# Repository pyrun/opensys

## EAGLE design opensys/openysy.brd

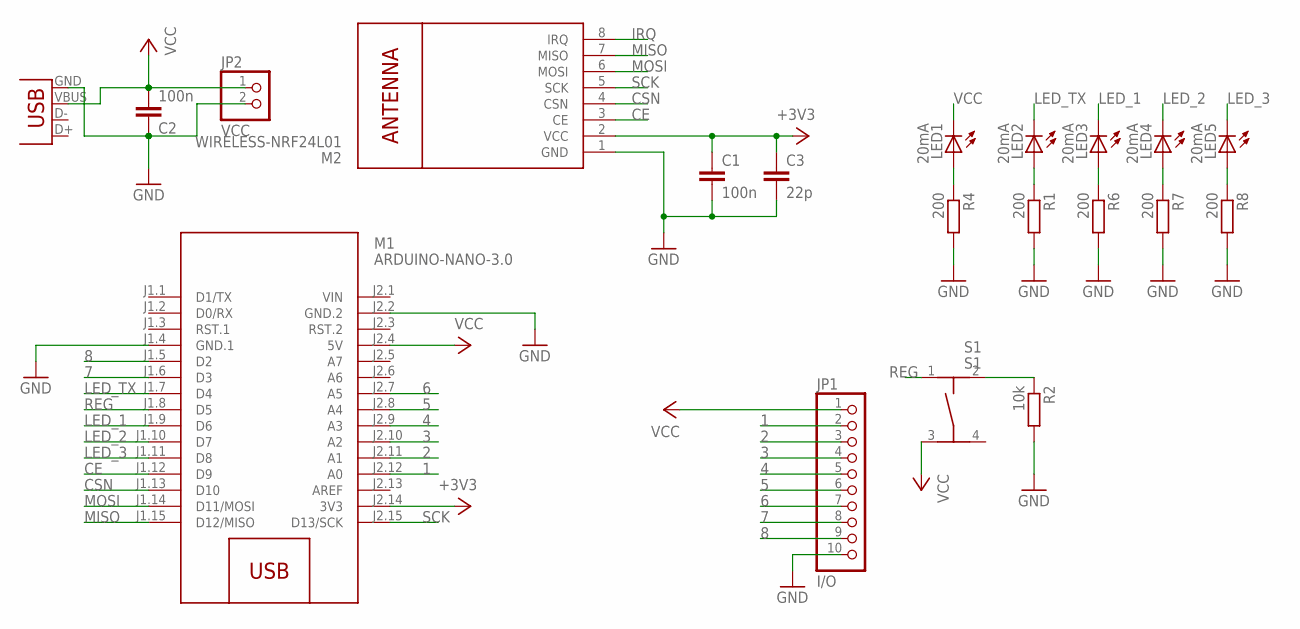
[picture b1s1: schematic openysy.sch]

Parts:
C1, C2: 100n; C1206
C3: 22p; C1206
JP1: I/O; 1X10
JP2: VCC; 1X02
LED1, LED2, LED3, LED4, LED5: 20mA; CHIPLED_1206
M1: ARDUINO-NANO-3.0
M2: WIRELESS-NRF24L01
R1, R4, R6, R7, R8: 200; R1206
R2: 10k; R1206
S1: S1; TASTER-9314_SMD
X2: USBPTH; USB-B-PTH

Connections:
1: JP1.2, M1.J2.12 (A0)
2: JP1.3, M1.J2.11 (A1)
3: JP1.4, M1.J2.10 (A2)
4: JP1.5, M1.J2.9 (A3)
5: JP1.6, M1.J2.8 (A4)
6: JP1.7, M1.J2.7 (A5)
7: JP1.8, M1.J1.6 (D3)
8: JP1.9, M1.J1.5 (D2)
+3V3: C1.1, C3.1, M1.J2.14 (3V3), M2.2 (VCC)
CE: M1.J1.12 (D9), M2.3 (CE)
CSN: M1.J1.13 (D10), M2.4 (CSN)
GND: C1.2, C2.1, C3.2, JP1.10, JP2.2, M1.J1.4 (GND.1), M1.J2.2 (GND.2), M2.1 (GND), R1.2, R2.2, R4.2, R6.2, R7.2, R8.2, X2.GND
IRQ: M2.8 (IRQ)
LED_1: LED3.C, M1.J1.9 (D6)
LED_2: LED4.C, M1.J1.10 (D7)
LED_3: LED5.C, M1.J1.11 (D8)
LED_TX: LED2.C, M1.J1.7 (D4)
MISO: M1.J1.15 (D12/MISO), M2.7 (MISO)
MOSI: M1.J1.14 (D11/MOSI), M2.6 (MOSI)
unnamed: LED2.A, R1.1
unnamed: LED1.A, R4.1
unnamed: R2.1, S1.2
unnamed: LED3.A, R6.1
unnamed: LED4.A, R7.1
unnamed: LED5.A, R8.1
REG: M1.J1.8 (D5), S1.1
SCK: M1.J2.15 (D13/SCK), M2.5 (SCK)
VCC: C2.2, JP1.1, JP2.1, LED1.C, M1.J2.4 (5V), S1.3, X2.VBUS
VIN: M1.J2.1 (VIN)

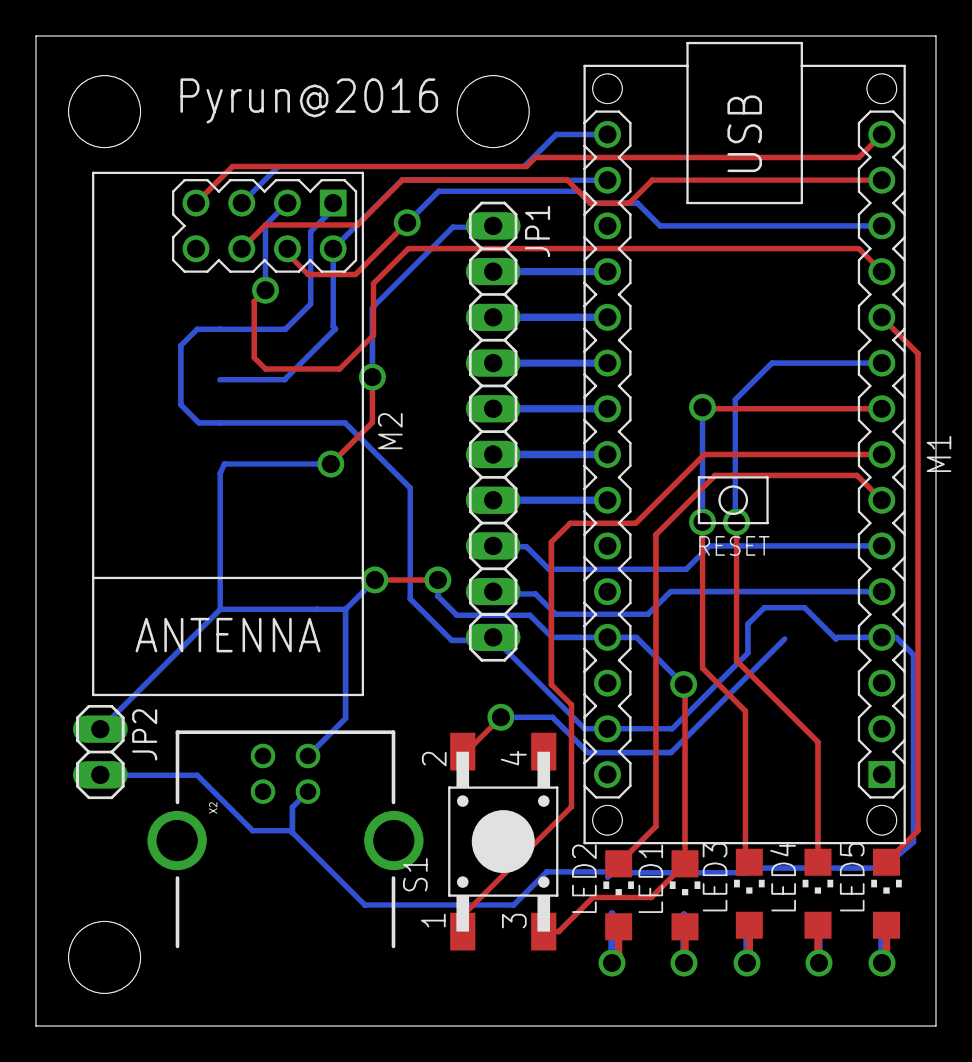
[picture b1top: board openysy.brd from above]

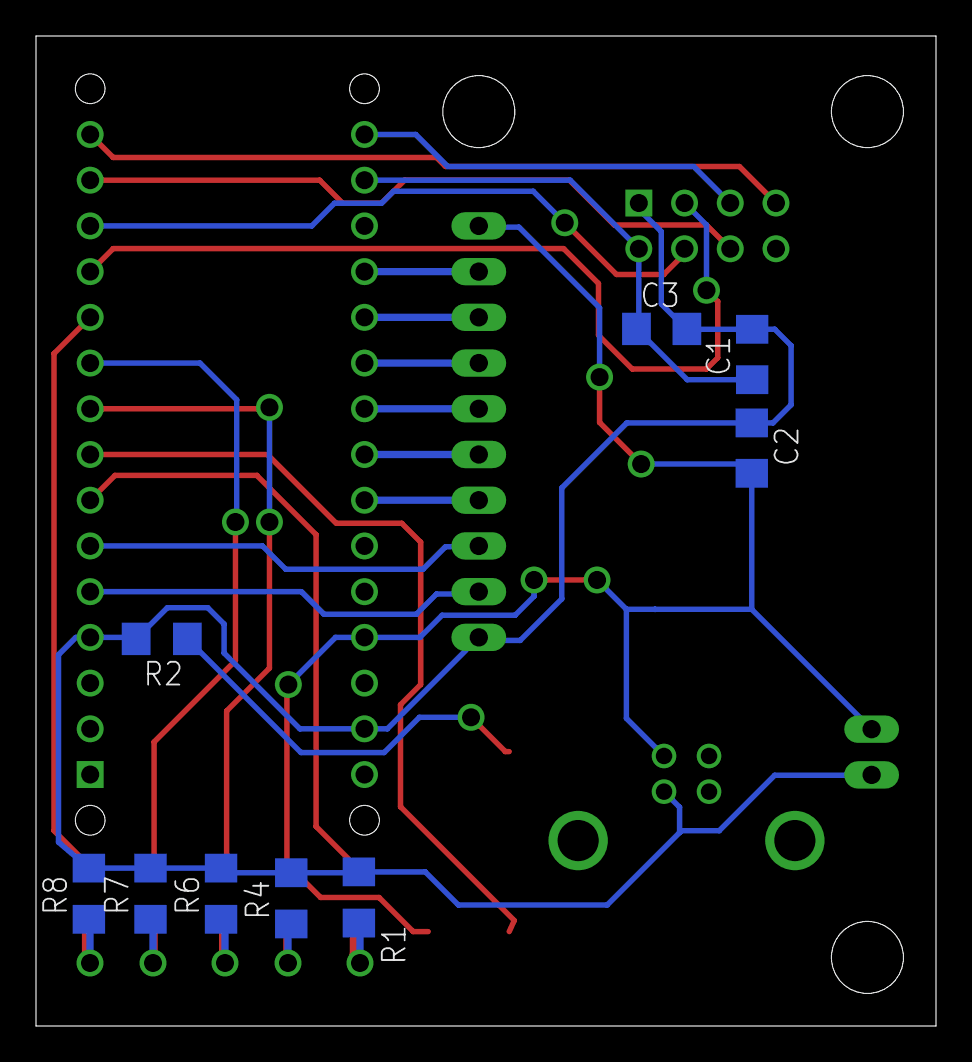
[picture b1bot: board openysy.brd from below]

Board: 2 copper layers, 50.0 x 55.0 mm, 20 parts (9 on the bottom side), 27 nets.

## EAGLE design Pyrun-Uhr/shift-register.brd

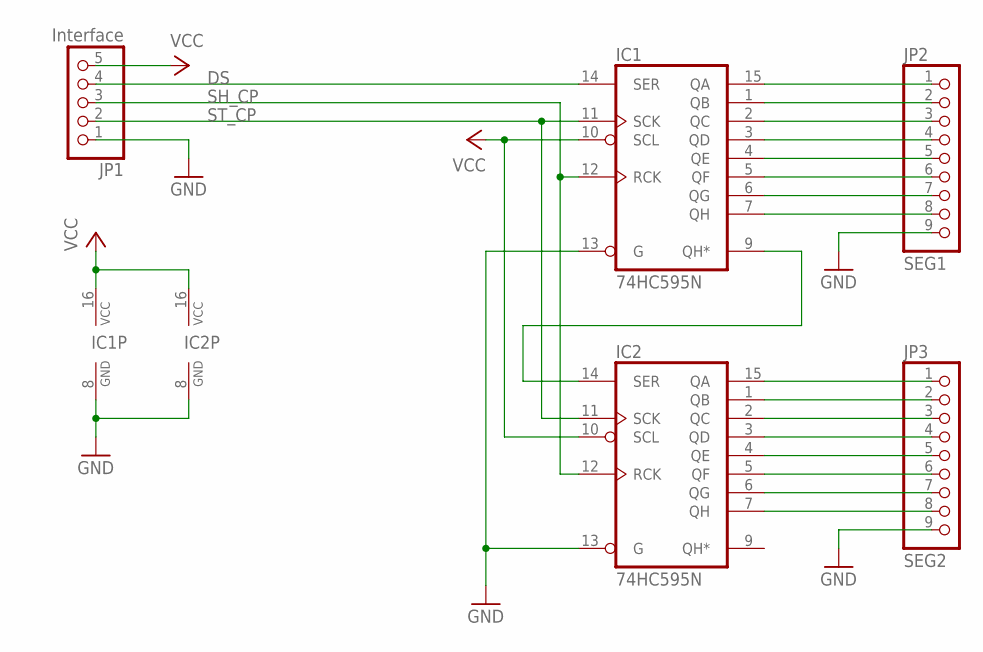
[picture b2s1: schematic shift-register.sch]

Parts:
IC1, IC2: 74HC595N; DIL16
JP1: Interface; 1X05
JP2: SEG1; 1X09
JP3: SEG2; 1X09

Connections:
DS: IC1.14 (SER), JP1.4
GND: IC1.8 (GND), IC1.13 (G), IC2.8 (GND), IC2.13 (G), JP1.1, JP2.9, JP3.9
unnamed: IC1.9 (QH*), IC2.14 (SER)
unnamed: IC1.15 (QA), JP2.1
unnamed: IC1.1 (QB), JP2.2
unnamed: IC1.2 (QC), JP2.3
unnamed: IC1.3 (QD), JP2.4
unnamed: IC1.4 (QE), JP2.5
unnamed: IC1.5 (QF), JP2.6
unnamed: IC1.6 (QG), JP2.7
unnamed: IC1.7 (QH), JP2.8
unnamed: IC2.15 (QA), JP3.1
unnamed: IC2.1 (QB), JP3.2
unnamed: IC2.2 (QC), JP3.3
unnamed: IC2.3 (QD), JP3.4
unnamed: IC2.4 (QE), JP3.5
unnamed: IC2.5 (QF), JP3.6
unnamed: IC2.6 (QG), JP3.7
unnamed: IC2.7 (QH), JP3.8
SH_CP: IC1.12 (RCK), IC2.12 (RCK), JP1.3
ST_CP: IC1.11 (SCK), IC2.11 (SCK), JP1.2
VCC: IC1.10 (SCL), IC1.16 (VCC), IC2.10 (SCL), IC2.16 (VCC), JP1.5

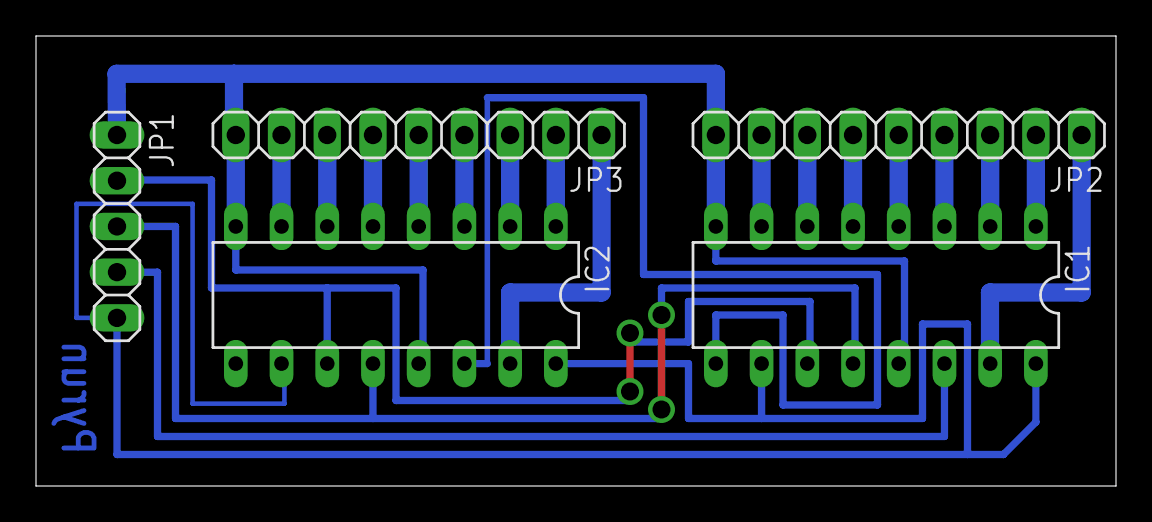
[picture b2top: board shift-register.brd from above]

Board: 2 copper layers, 60.0 x 25.0 mm, 5 parts (0 on the bottom side), 22 nets.

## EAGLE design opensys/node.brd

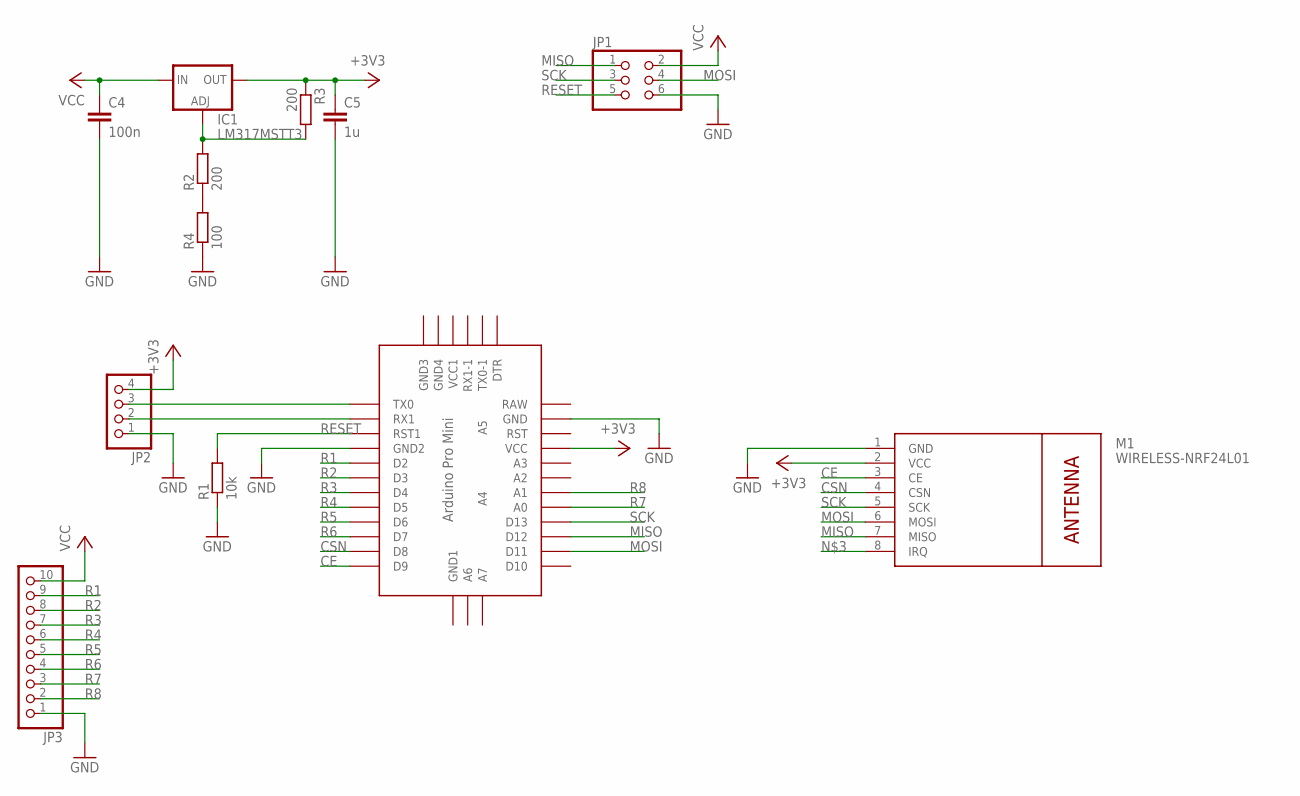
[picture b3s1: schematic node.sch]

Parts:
C4: 100n; C1206
C5: 1u; C1206
IC1: LM317MSTT3; SOT223
JP1: PINHD-2X3; 2X03
JP2: PINHD-1X4; 1X04
JP3: PINHD-1X10; 1X10
M1: WIRELESS-NRF24L01
R1: 10k; M1206
R2, R3: 200; M1206
R4: 100; M1206
U$1: ABK-PRO-MINI

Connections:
+3V3: C5.1, IC1.4 (OUT), JP2.4, M1.2 (VCC), R3.1, U$1.VCC
ADJ_V3: IC1.1 (ADJ), R2.2, R3.2
CE: M1.3 (CE), U$1.D9
CSN: M1.4 (CSN), U$1.D8
GND: C4.2, C5.2, JP1.6, JP2.1, JP3.1, M1.1 (GND), R1.1, R4.1, U$1.GND, U$1.GND1 (GND2)
MISO: JP1.1, M1.7 (MISO), U$1.D12
MOSI: JP1.4, M1.6 (MOSI), U$1.D11
unnamed: JP2.3, U$1.TX0
unnamed: JP2.2, U$1.RX1
unnamed: R2.1, R4.2
R1: JP3.9, U$1.D2
R2: JP3.8, U$1.D3
R3: JP3.7, U$1.D4
R4: JP3.6, U$1.D5
R5: JP3.5, U$1.D6
R6: JP3.4, U$1.D7
R7: JP3.3, U$1.A0
R8: JP3.2, U$1.A1
RESET: JP1.5, R1.2, U$1.RST1
SCK: JP1.3, M1.5 (SCK), U$1.D13
VCC: C4.1, IC1.3 (IN), JP1.2, JP3.10

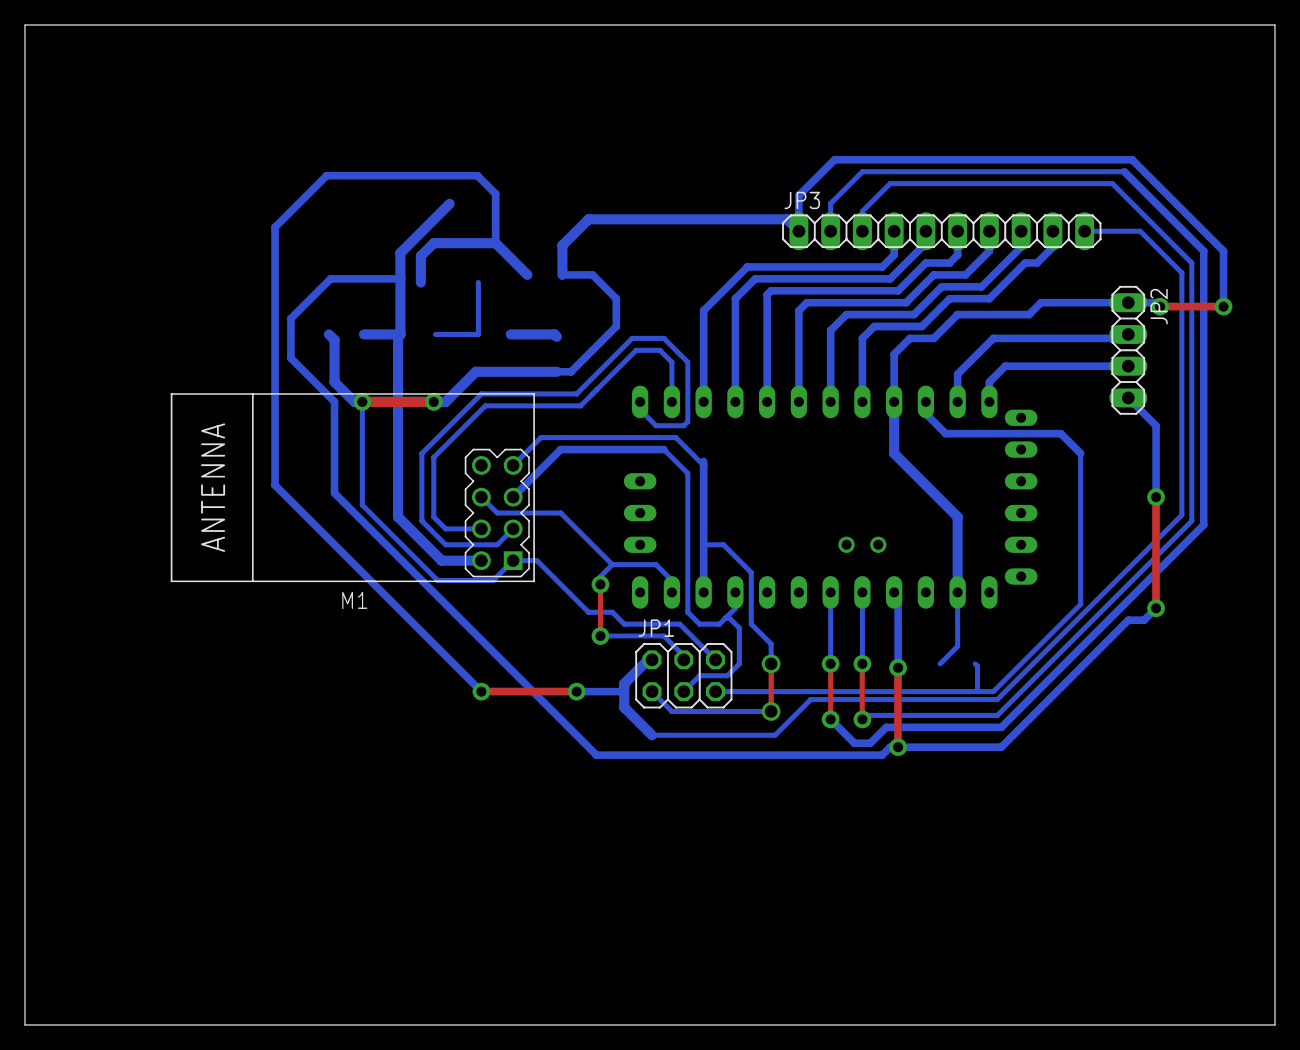
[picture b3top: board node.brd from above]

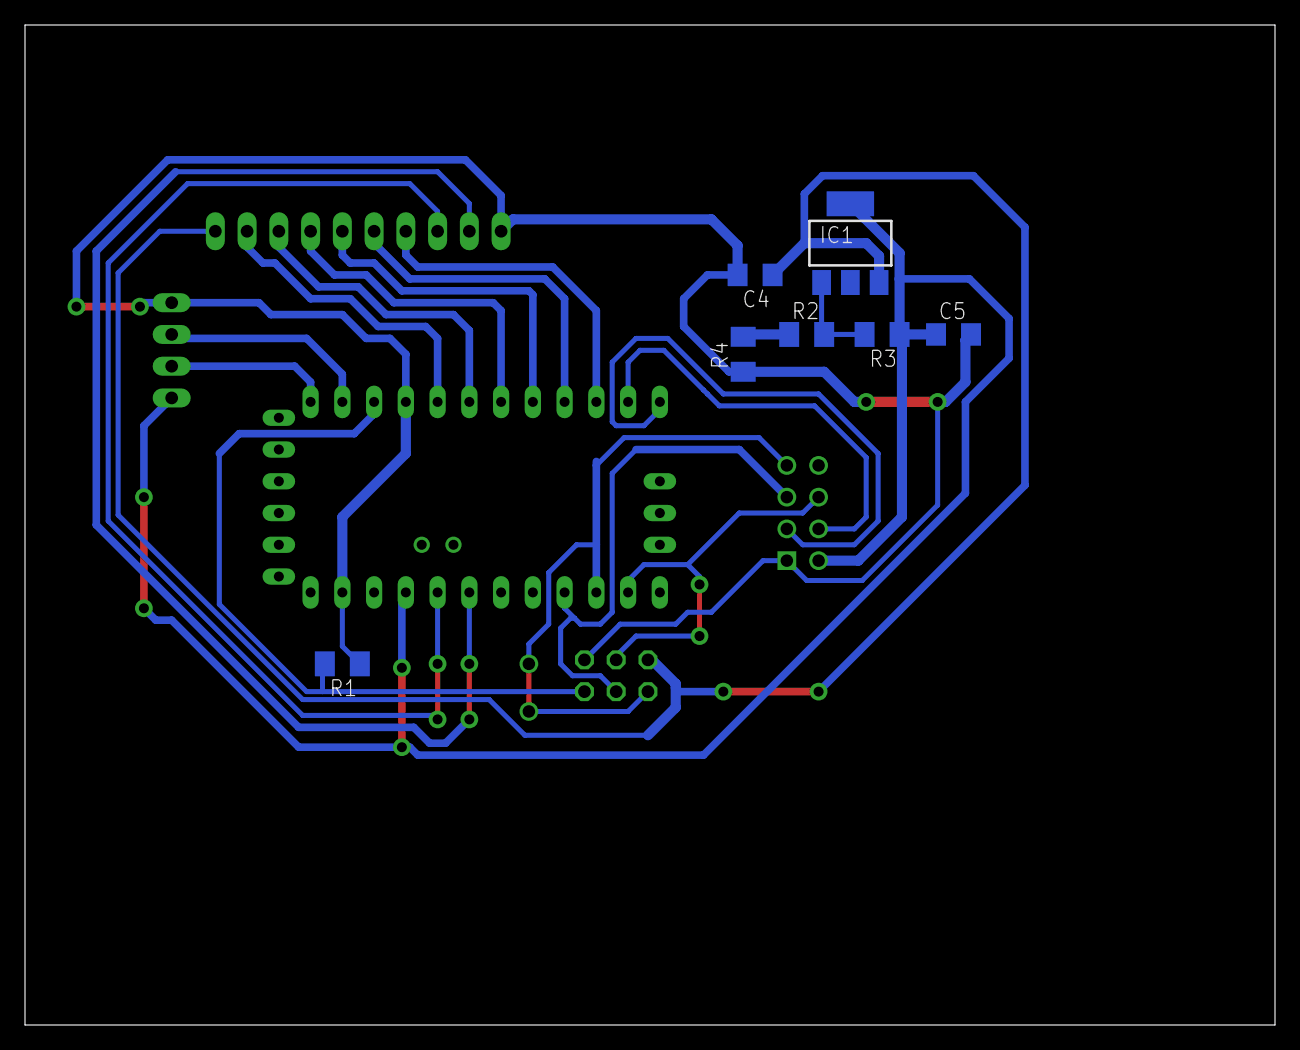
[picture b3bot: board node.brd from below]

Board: 2 copper layers, 100.0 x 80.0 mm, 12 parts (7 on the bottom side), 21 nets.

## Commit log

2016-02-11 test git debian
2016-02-11 splitt in two files
2016-05-21 :neckbeard: Added .gitattributes & .gitignore files
2016-05-21 main init
2016-05-21 rewrite stack
    output work now with rf - example
2016-06-14 Arduino Nano Update
2016-07-19 add eagle
2016-08-05 change board - now v1.0
2016-08-16 add binnary uhr
2016-08-20 smart home platine now v3
    lets try it now

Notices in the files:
parts and their libraries:
diy-modules: Released under the Creative Commons Attribution 4.0 International License: http://creativecommons.org/licenses/by/4.0
